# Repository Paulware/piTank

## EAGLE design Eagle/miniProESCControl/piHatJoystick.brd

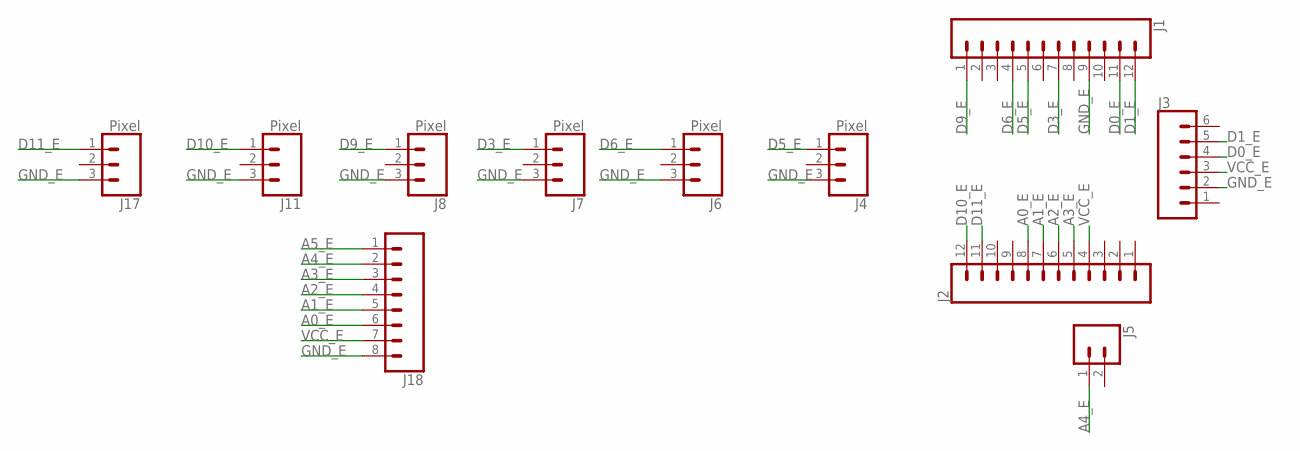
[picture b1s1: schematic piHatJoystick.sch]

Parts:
J1, J2: CONN_12; 1X12
J3: CONN_06SILK_FEMALE_PTH; 1X06
J4, J6, J7, J8, J11, J17: Pixel; 1X03
J5: CONN_02; 1X02
J18: CONN_08"; 1X08

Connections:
A0_E: J2.8, J18.6
A1_E: J2.7, J18.5
A2_E: J2.6, J18.4
A3_E: J2.5, J18.3
A4_E: J5.1, J18.2
A5_E: J18.1
D0_E: J1.11, J3.4
D1_E: J1.12, J3.5
D3_E: J1.7, J7.1
D5_E: J1.5, J4.1
D6_E: J1.4, J6.1
D9_E: J1.1, J8.1
D10_E: J2.12, J11.1
D11_E: J2.11, J17.1
GND_E: J1.9, J3.2, J4.3, J6.3, J7.3, J8.3, J11.3, J17.3, J18.8
VCC_E: J2.4, J3.3, J18.7

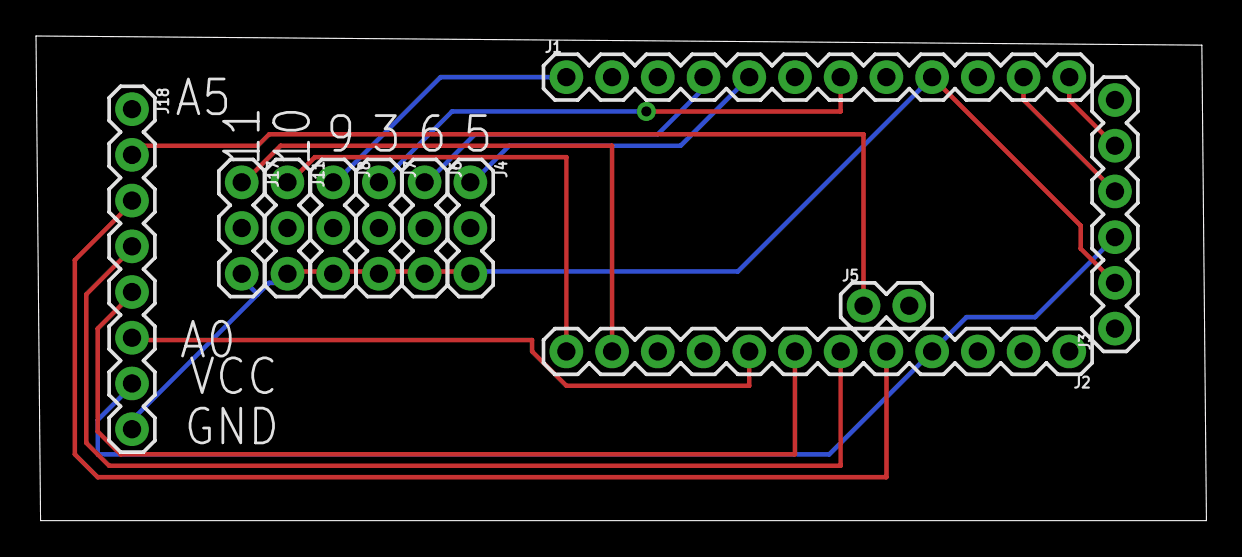
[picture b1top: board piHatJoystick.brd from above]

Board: 2 copper layers, 65.0 x 26.9 mm, 11 parts (0 on the bottom side), 15 nets.

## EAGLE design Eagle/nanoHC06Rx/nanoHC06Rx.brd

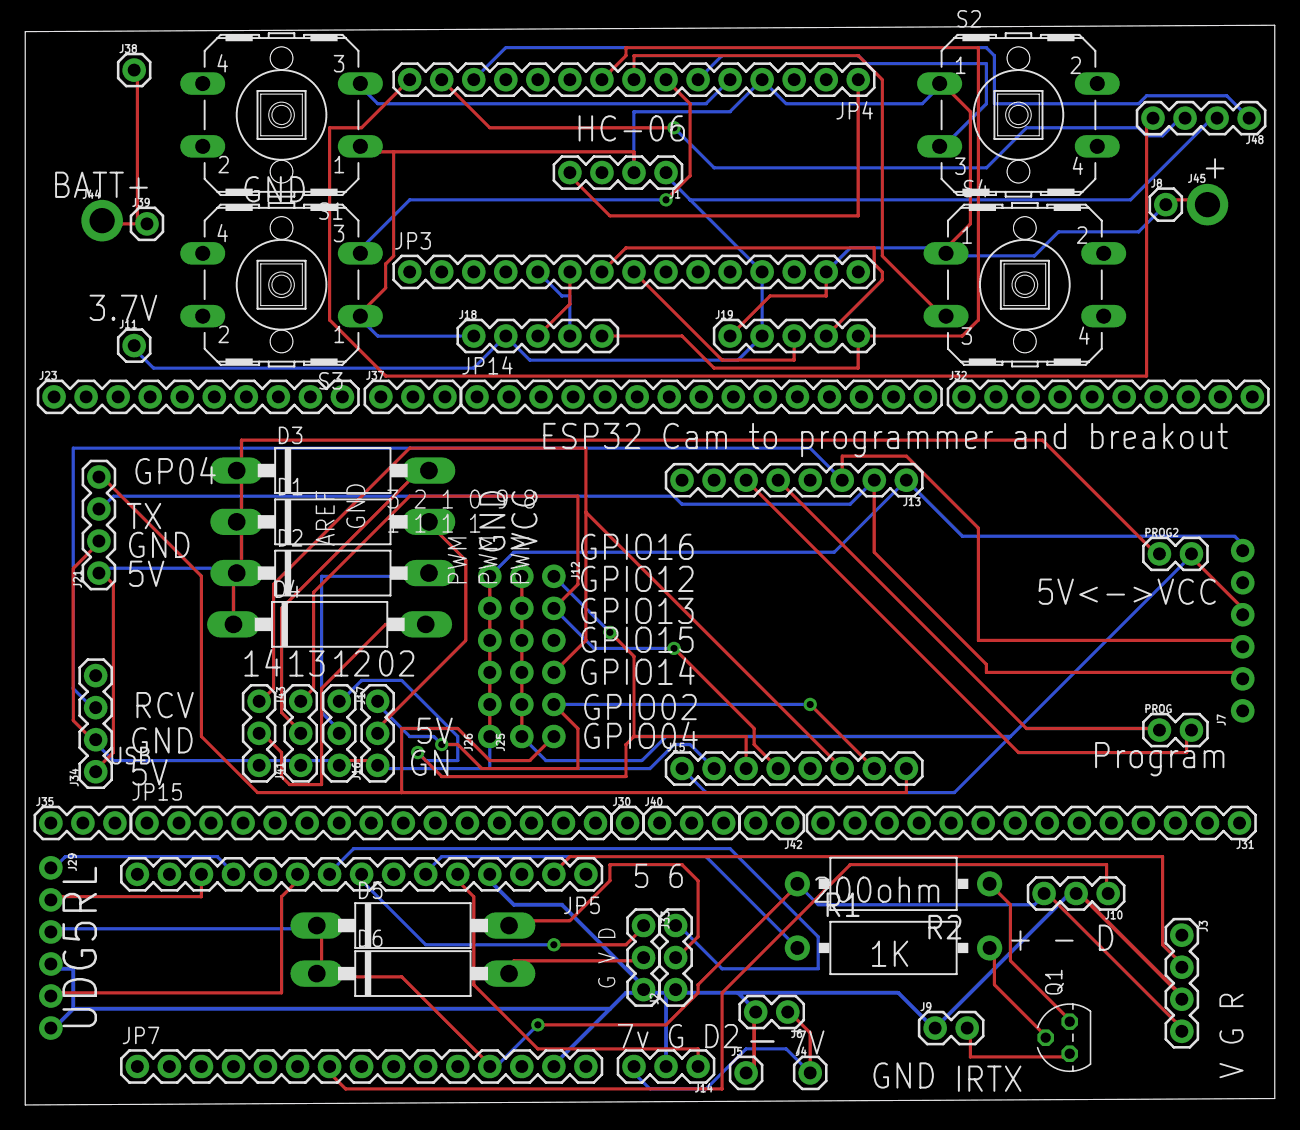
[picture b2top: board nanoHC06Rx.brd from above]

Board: 2 copper layers, 99.1 x 85.6 mm, 61 parts (0 on the bottom side), 49 nets.

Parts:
D1, D2, D3, D4, D5, D6: 1N5333; C1702-15
J1, J3, J21, J34, J48: 1X04
J2, J10, J14, J16, J17, J33, J41, J43: Relay; 1X03
J4, J5, J8, J11, J30, J38, J39: 1X01
J6, J9, J42: 1X02
J7, J12, J25, J26, J29: 1X06_NO_SILK
J13, J15: 1X08
J18, J19: 1X05
J23, J32: 1X10
J31: 1X14
J35, J37, J40: 1X03
J44, J45: 1X01_2MM
JP3, JP4, JP5, JP7, JP14, JP15: 1X15@1
PROG, PROG2: 1X02
Q1: 2N5088; TO92
R1, R2: 1K; CA0001
S1, S2, S3, S4: B3F-40XX

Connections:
5V_B: D1.C, D2.C, D3.C, D4.C, J21.1, J34.1, PROG2.1
7.4V: J4.1, J6.1, J14.3
A1_D: J18.4, JP3.5
A2_D: J18.3, JP3.6
A3_D: J19.4, JP3.7
A4_D: J19.3, JP3.8
BATT_3V3_D: J38.1, J39.1, J44.1
D0: J3.2, JP5.2
D2: J14.1, JP5.5
D2_D: JP4.5, S1.3
D3: JP5.6, R1.1
D3_D: JP4.6, S2.3
D4_D: JP4.7, S3.3
D5: J33.1, JP5.8
D5_D: JP4.8, S4.3
D6: J2.3, JP5.9
D6_D: J18.5, J19.5, JP4.9
D7: J29.5, JP5.10
D9: J29.1, JP5.12
D10: J29.2, JP5.13
D10_D: J48.1, JP4.13
D11_D: J48.3, JP4.14
D12_D: J48.4, JP4.15
D17: J10.1, JP7.7
GND: J2.1, J3.3, J5.1, J6.2, J9.1, J10.2, J14.2, J29.4, J29.6, J33.3, JP5.4, JP7.14
GND_B: J7.6, J13.1, J15.2, J16.1, J17.3, J21.2, J26.1, J26.2, J26.3, J26.4, J26.5, J26.6, J34.2, J41.1, J43.3
GND_D: J1.2, J8.1, J18.1, J19.1, J45.1, JP3.14, JP4.4, S1.1, S2.1, S3.1, S4.1
GPIO02_B: J12.5, J15.7, J16.3
GPIO04_B: J12.6, J15.8, J21.4
GPIO12_B: J12.1, J15.3, J17.1
GPIO13_B: J12.2, J15.4, J41.3
GPIO14_B: J12.4, J15.6, J43.1
IRTX: J9.2, Q1.3
unnamed: Q1.2, R1.2
unnamed: D1.A, J16.2
unnamed: Q1.1, R2.1
unnamed: D2.A, J17.2
unnamed: D3.A, J41.2
unnamed: D4.A, J43.2
unnamed: D5.A, J2.2
unnamed: D6.A, J33.2
PROG1: J13.5, PROG.1
PROG2: J13.6, PROG.2
TX_D: J1.4, JP4.1
UOR: J7.3, J13.3, J34.3
UOT: J7.2, J13.2, J21.3
VCC: D5.C, D6.C, J3.4, J10.3, J29.3, JP7.12, R2.2
VCC_B: J7.4, J15.1, J25.1, J25.2, J25.3, J25.4, J25.5, J25.6, PROG2.2
VCC_D: J1.1, J11.1, J18.2, J19.2, J48.2, JP3.12

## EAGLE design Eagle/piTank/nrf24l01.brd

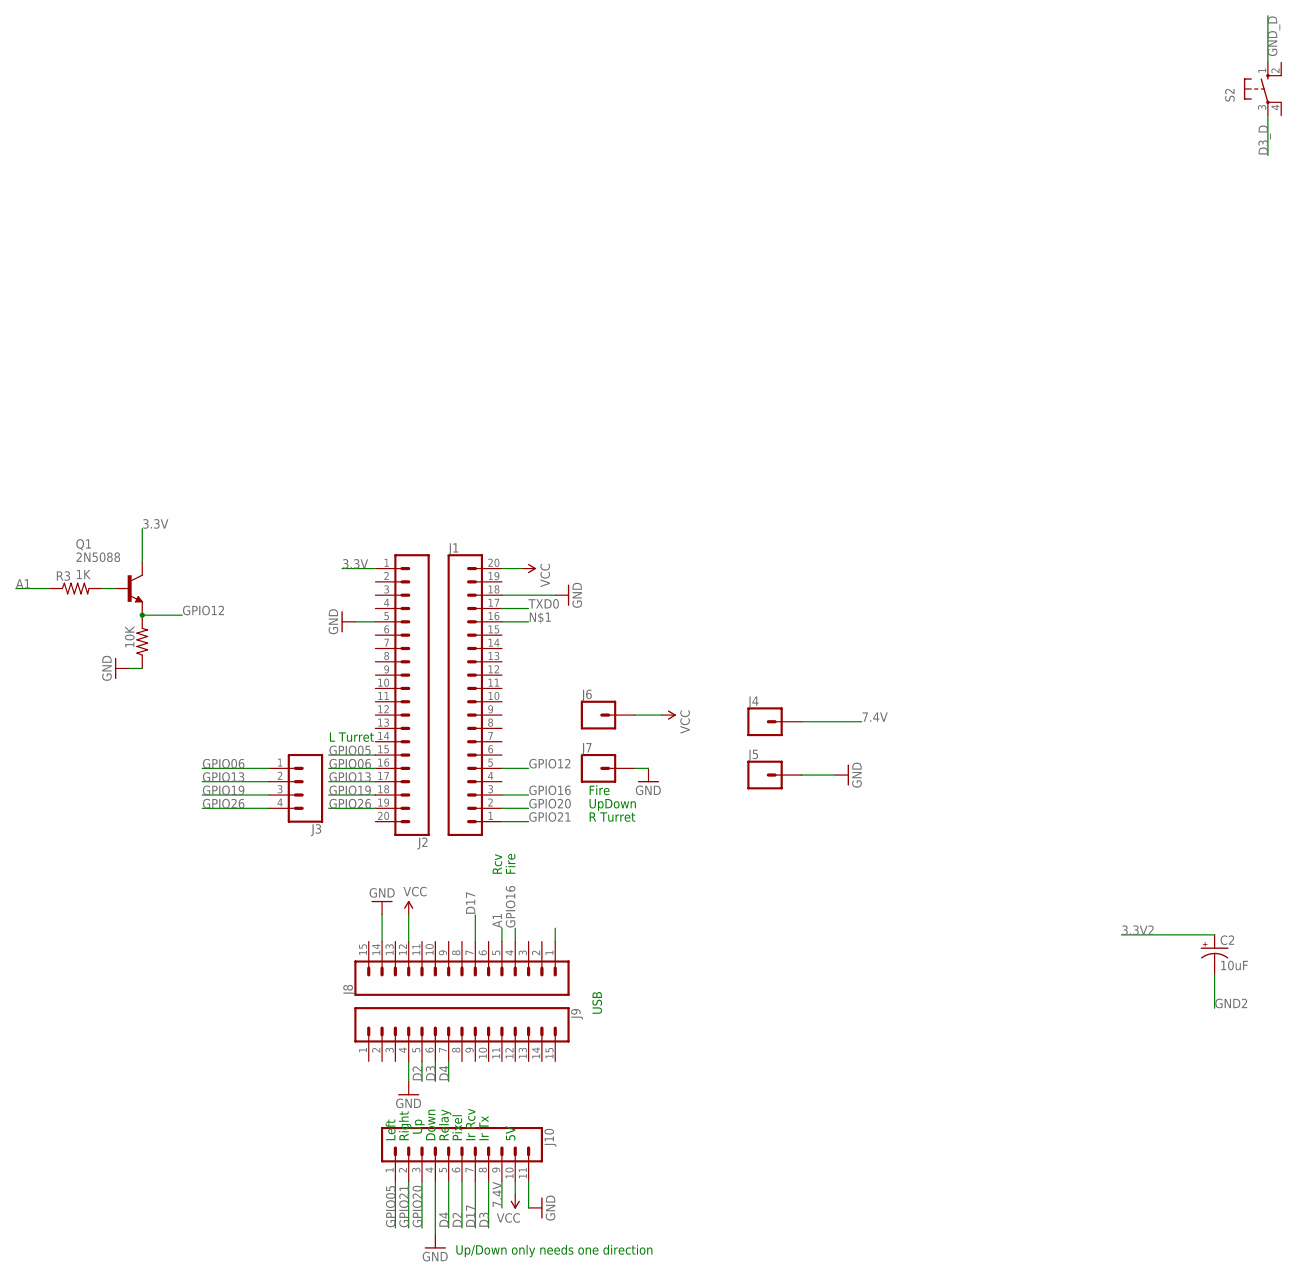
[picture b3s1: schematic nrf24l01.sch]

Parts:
10K: 10K; 0207/12
C2: 10uF; CPOL-RADIAL-2.5MM-5MM
J1, J2: CONN_20; 1X20
J3: CONN_04; 1X04
J4, J5, J6, J7: CONN_01; 1X01
J8, J9: CONN_15; 1X15
J10: CONN_11; 1X11
Q1: 2N5088; TO92
R3: 1K; 0207/12
S2: 40-XX; B3F-40XX

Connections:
3.3V: J2.1, Q1.1 (C)
3.3V2: C2.1 (+)
7.4V: J4.1, J10.9
A1: J8.5, R3.1
D2: J9.5, J10.6
D3: J9.6, J10.8
D3_D: S2.3
D4: J9.7, J10.5
D17: J8.7, J10.7
GND: 10K.1, J1.18, J2.5, J5.1, J7.1, J8.14, J9.4, J10.4, J10.11
GND2: C2.2 (-)
GND_D: S2.1 (S)
GPIO05: J2.15, J10.1
GPIO06: J2.16, J3.1
GPIO12: 10K.2, J1.5, Q1.3 (E)
GPIO13: J2.17, J3.2
GPIO16: J1.3, J8.4
GPIO19: J2.18, J3.3
GPIO20: J1.2, J10.3
GPIO21: J1.1, J10.2
GPIO26: J2.19, J3.4
unnamed: Q1.2 (B), R3.2
TXD0: J1.17
VCC: J1.20, J6.1, J8.12, J10.10

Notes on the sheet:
Fire
Rcv
USB
Up/Down only needs one direction
Left
Right
Down
Relay
Pixel
Ir Rcv
Ir Tx
UpDown
R Turret
L Turret

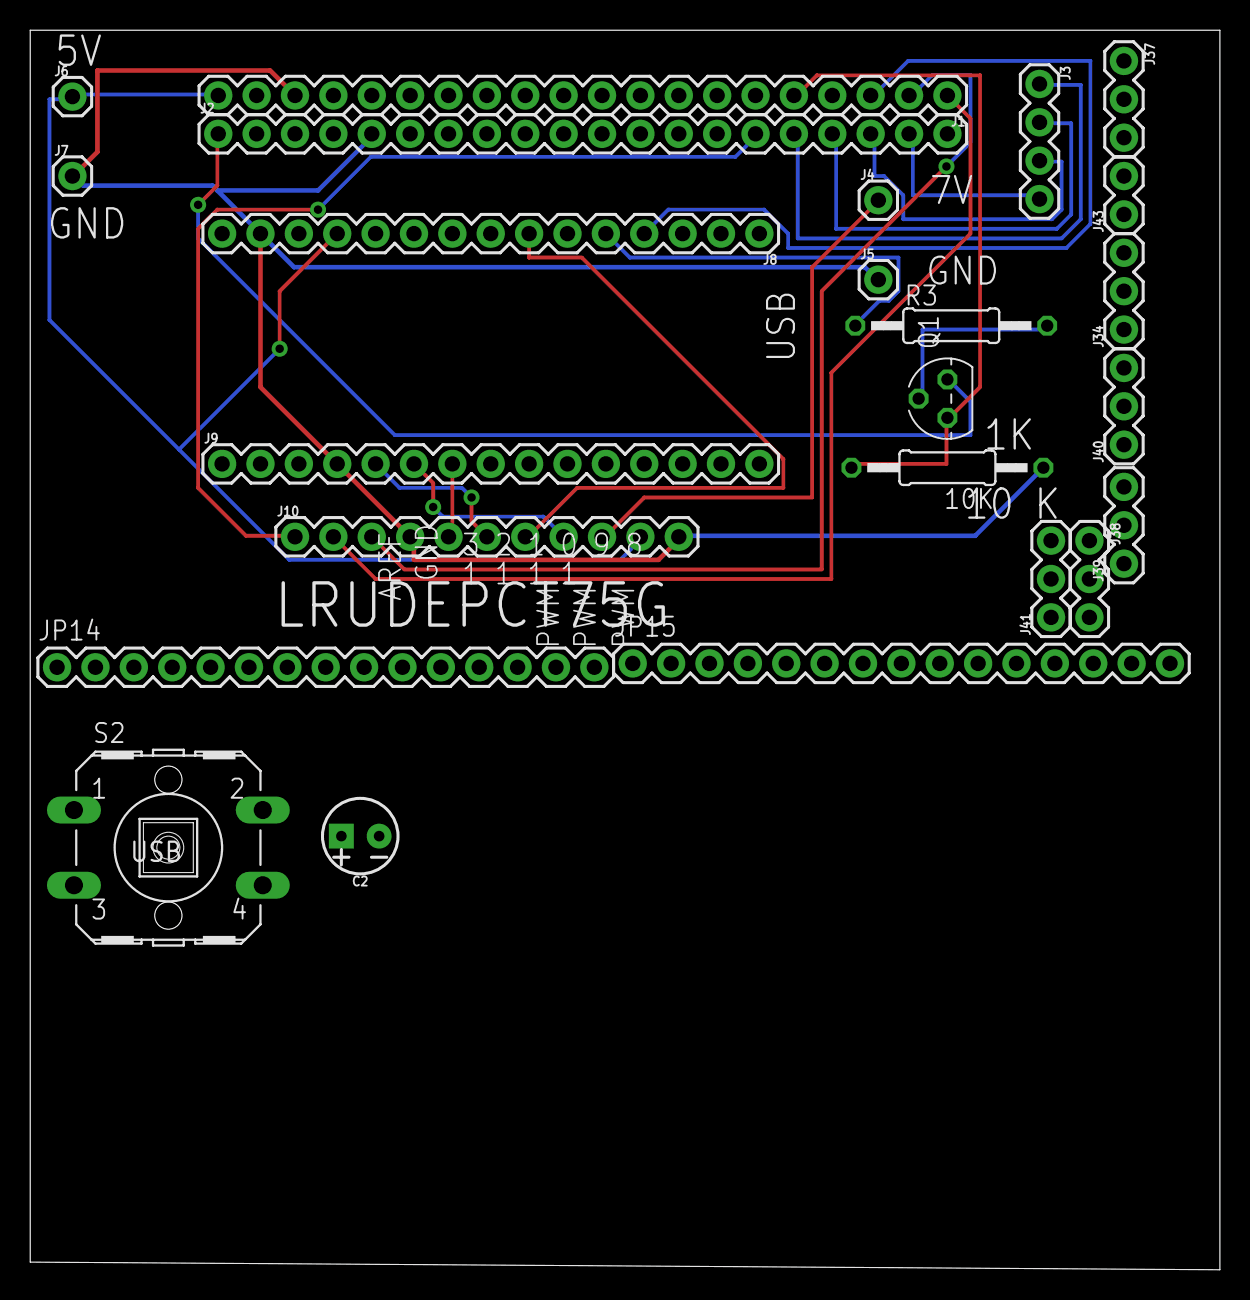
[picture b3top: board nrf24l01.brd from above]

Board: 2 copper layers, 78.7 x 82.0 mm, 24 parts (0 on the bottom side), 19 nets.

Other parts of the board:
J34, J37, J38, J39, J40, J41: 1X03
J43: 1X02
JP14, JP15: 1X15

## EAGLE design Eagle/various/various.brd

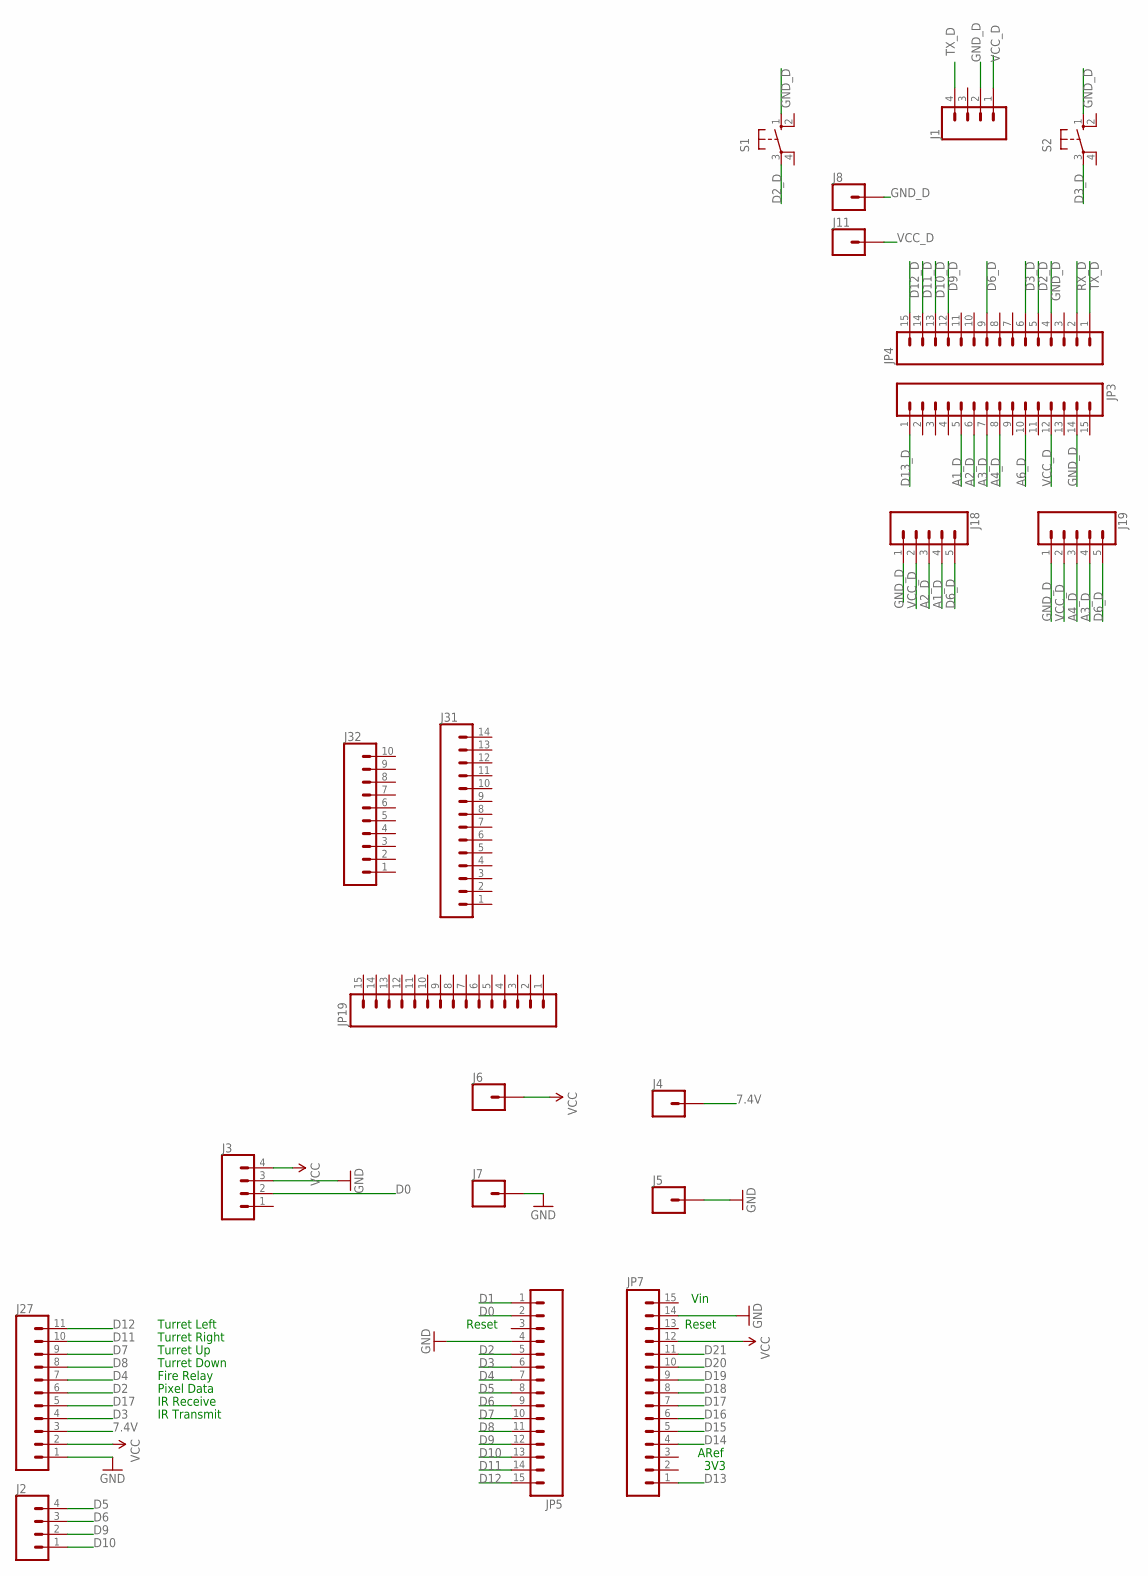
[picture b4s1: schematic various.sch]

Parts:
J1, J2, J3: CONN_04; 1X04
J4, J5, J6, J7, J8, J11: CONN_01; 1X01
J18, J19: CONN_05; 1X05
J27: CONN_11; 1X11
J31: CONN_14; 1X14
J32: CONN_10"; 1X10
JP3, JP4, JP5, JP7, JP19: M15; 1X15
S1, S2: 40-XX; B3F-40XX

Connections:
7.4V: J4.1, J27.3
A1_D: J18.4, JP3.5
A2_D: J18.3, JP3.6
A3_D: J19.4, JP3.7
A4_D: J19.3, JP3.8
A6_D: JP3.10
D0: J3.2, JP5.2
D1: JP5.1
D2: J27.6, JP5.5
D2_D: JP4.5, S1.3
D3: J27.4, JP5.6
D3_D: JP4.6, S2.3
D4: J27.7, JP5.7
D5: J2.4, JP5.8
D6: J2.3, JP5.9
D6_D: J18.5, J19.5, JP4.9
D7: J27.9, JP5.10
D8: J27.8, JP5.11
D9: J2.2, JP5.12
D9_D: JP4.12
D10: J2.1, JP5.13
D10_D: JP4.13
D11: J27.10, JP5.14
D11_D: JP4.14
D12: J27.11, JP5.15
D12_D: JP4.15
D13: JP7.1
D13_D: JP3.1
D14: JP7.4
D15: JP7.5
D16: JP7.6
D17: J27.5, JP7.7
D18: JP7.8
D19: JP7.9
D20: JP7.10
D21: JP7.11
GND: J3.3, J5.1, J7.1, J27.1, JP5.4, JP7.14
GND_D: J1.2, J8.1, J18.1, J19.1, JP3.14, JP4.4, S1.1 (S), S2.1 (S)
RX_D: JP4.2
TX_D: J1.4, JP4.1
VCC: J3.4, J6.1, J27.2, JP7.12
VCC_D: J1.1, J11.1, J18.2, J19.2, JP3.12

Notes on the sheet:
Reset
Vin
ARef
3V3
Turret Left
Turret Right
Turret Up
Turret Down
Fire Relay
Pixel Data
IR Receive
IR Transmit

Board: 2 copper layers, 32 parts (0 on the bottom side), 26 nets, no tracks yet.

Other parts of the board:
J34, J35, J37, J38, J39, J40, J41: 1X03
J42, J43: 1X02
JP14, JP15: 1X15

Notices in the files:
parts and their libraries:
SparkFun-Connectors: Licensing: Creative Commons ShareAlike 4.0 International - https://creativecommons.org/licenses/by-sa/4.0
